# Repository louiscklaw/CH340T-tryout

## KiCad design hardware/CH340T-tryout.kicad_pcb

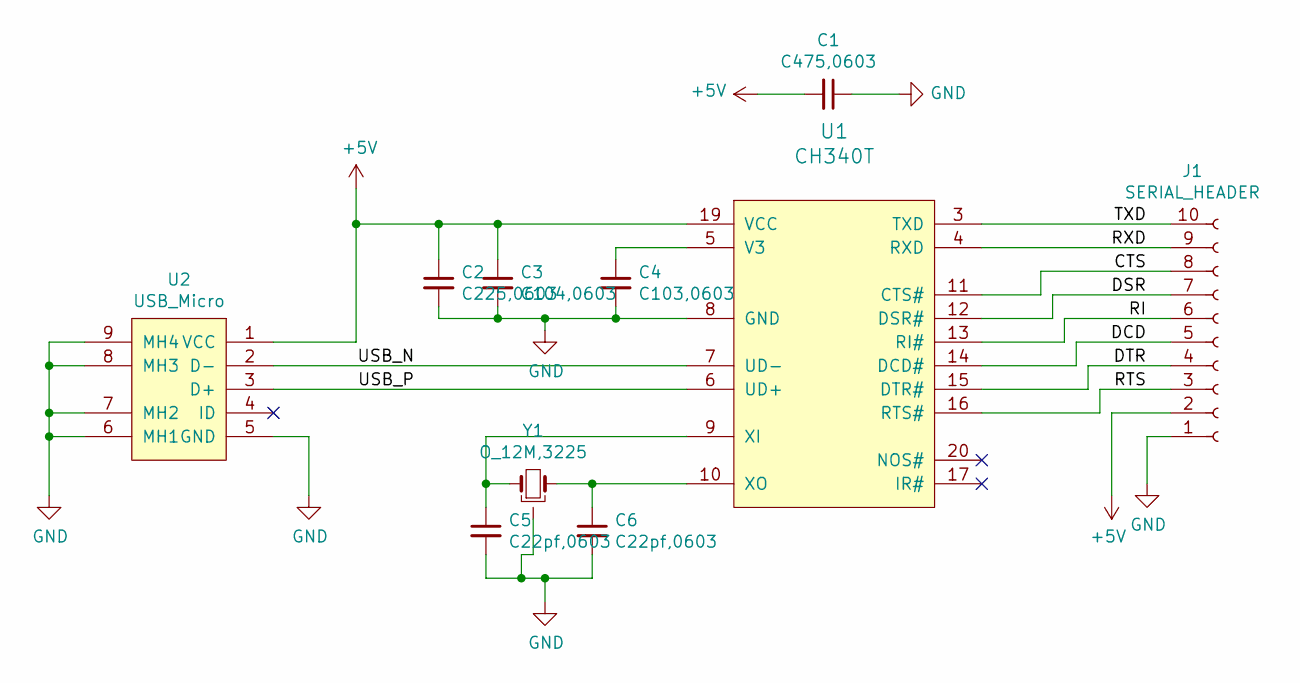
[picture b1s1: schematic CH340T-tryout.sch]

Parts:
C1: C475,0603; C_0603_1608Metric_Pad1.05x0.95mm_HandSolder
C2: C225,0603; C_0603_1608Metric_Pad1.05x0.95mm_HandSolder
C3: C104,0603; C_0603_1608Metric_Pad1.05x0.95mm_HandSolder
C4: C103,0603; C_0603_1608Metric_Pad1.05x0.95mm_HandSolder
C5, C6: C22pf,0603; C_0603_1608Metric_Pad1.05x0.95mm_HandSolder
J1: SERIAL_HEADER; PinHeader_1x10_P1.27mm_Vertical
U1: CH340T; CH340T_SSOP-20
U2: USB_Micro; USB_Micro-B_Molex-105017-0001
Y1: O_12M,3225; OSC_3225

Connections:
+5V: C1.2, C2.1, C3.1, J1.2, U1.19 (VCC), U2.1 (VCC)
/CTS: J1.8, U1.11 (CTS#)
/DCD: J1.5, U1.14 (DCD#)
/DSR: J1.7, U1.12 (DSR#)
/DTR: J1.4, U1.15 (DTR#)
/RI: J1.6, U1.13 (RI#)
/RTS: J1.3, U1.16 (RTS#)
/RXD: J1.9, U1.4 (RXD)
/TXD: J1.10, U1.3 (TXD)
/USB_N: U1.7 (UD-), U2.2 (D-)
/USB_P: U1.6 (UD+), U2.3 (D+)
GND: C1.1, C2.2, C3.2, C4.2, C5.2, C6.2, J1.1, U1.8 (GND), U2.5 (GND), U2.6 (MH1), U2.7 (MH2), U2.8 (MH3), U2.9 (MH4), Y1.2
unnamed: C4.1, U1.5 (V3)
unnamed: C5.1, U1.9 (XI), Y1.1
unnamed: C6.1, U1.10 (XO), Y1.3

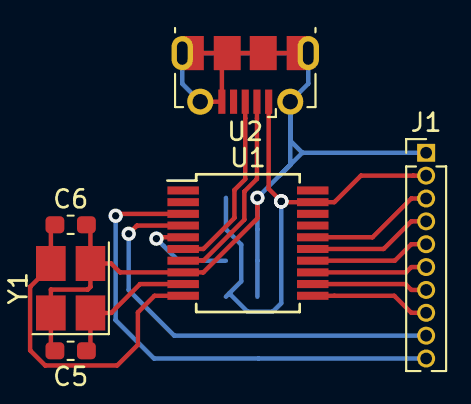
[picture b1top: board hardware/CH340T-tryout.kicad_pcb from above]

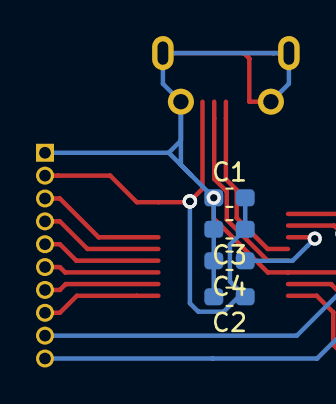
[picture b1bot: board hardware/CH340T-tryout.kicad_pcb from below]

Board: 2 copper layers, 10 parts (4 on the bottom side), 15 nets.

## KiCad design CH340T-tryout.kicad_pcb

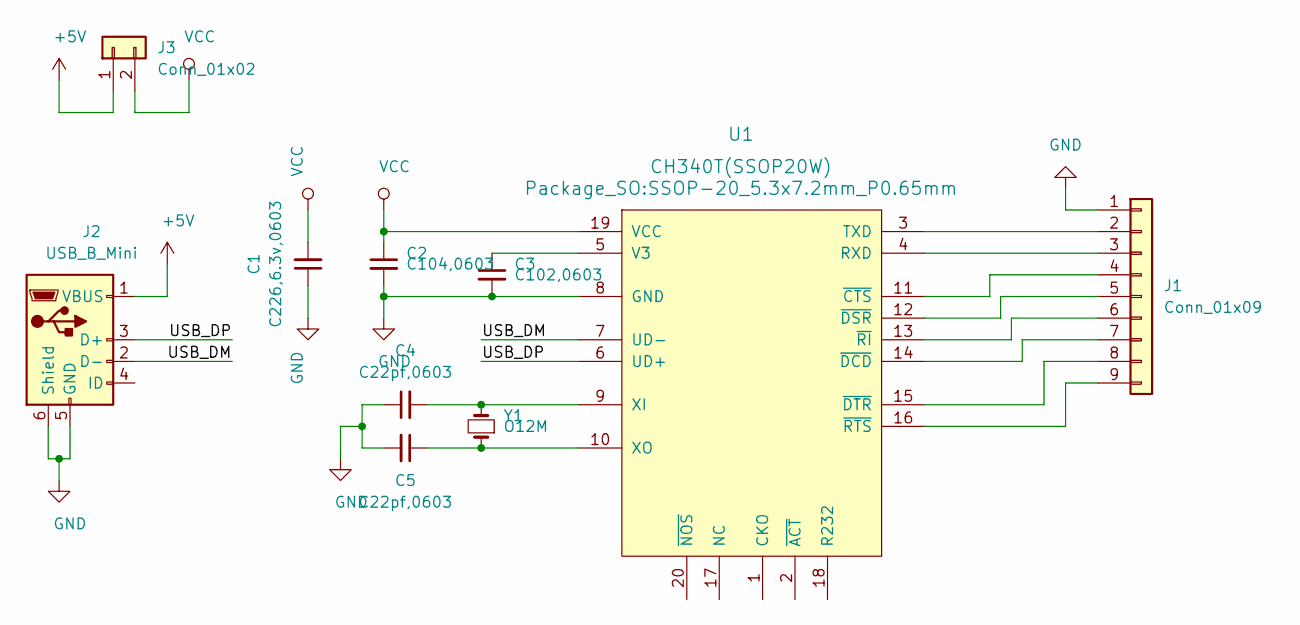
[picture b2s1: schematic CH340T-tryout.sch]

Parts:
C1: C226,6.3v,0603; C_0603_1608Metric_Pad1.05x0.95mm_HandSolder
C2: C104,0603; C_0603_1608Metric_Pad1.05x0.95mm_HandSolder
C3: C102,0603; C_0603_1608Metric_Pad1.05x0.95mm_HandSolder
C4, C5: C22pf,0603; C_0603_1608Metric_Pad1.05x0.95mm_HandSolder
J1: Conn_01x09; PinHeader_1x09_P1.27mm_Vertical
J2: USB_B_Mini; USB_Micro-B_Molex_47346-0001
J3: Conn_01x02; PinHeader_1x02_P1.27mm_Vertical
U1: CH340T(SSOP20W); SSOP-20_5.3x7.2mm_P0.65mm
Y1: O12M; crystal_hc-49s

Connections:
+5V: J2.1 (VBUS), J3.1
/USB_DM: J2.2 (D-), U1.7 (UD-)
/USB_DP: J2.3 (D+), U1.6 (UD+)
GND: C1.1, C2.2, C3.2, C4.1, C5.2, J1.1, J2.5 (GND), J2.6 (Shield), U1.8 (GND)
unnamed: C3.1, U1.5 (V3)
unnamed: C4.2, U1.9 (XI), Y1.2
unnamed: C5.1, U1.10 (XO), Y1.1
unnamed: J1.2, U1.3 (TXD)
unnamed: J1.3, U1.4 (RXD)
unnamed: J1.4, U1.11 (~CTS~)
unnamed: J1.5, U1.12 (~DSR~)
unnamed: J1.6, U1.13 (~RI~)
unnamed: J1.7, U1.14 (~DCD~)
unnamed: J1.8, U1.15 (~DTR~)
unnamed: J1.9, U1.16 (~RTS~)
VCC: C1.2, C2.1, J3.2, U1.19 (VCC)

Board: 2 copper layers, 10 parts (6 on the bottom side), 16 nets, no tracks yet.

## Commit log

2018-12-16 update,
2019-06-23 update to ignore bak files,
2020-05-05 ci: init travis token,
2020-05-05 ci: init travis build config,
